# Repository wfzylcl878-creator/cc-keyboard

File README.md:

# CC-Keyboard — 6 键蓝牙小键盘

方向键 + 回车 + ESC 的紧凑蓝牙小键盘。布局（两行 + 右侧竖跨 2u 回车）：

```
┌───┐      ┌───┐
│ESC│  ↑   │ ↵ │
└───┘      │   │
┌───┬───┬───┐   │
│ ← │ ↓ │ → │   │
└───┴───┴───┤   │
            └───┘
┌───────────┴────────────────────┐
│ 电池   [SuperMini 横放 USB←]  开关 │  ← 底部凸出区
└────────────────────────────────┘
```

主控 SuperMini nRF52840（排针插接可拆卸，躺平在底部凸出区、USB 朝左），ZMK 固件，热插拔轴座。

## 目录结构

```
cc-keyboard/
├── ergogen/config.yaml      # PCB 生成配置（改布局/接线就改它）
├── output/                  # 生成产物（可随时重新生成）
│   ├── pcbs/main.kicad_pcb  #   PCB（嘉立创打样直接上传）
│   ├── outlines/plate.dxf   #   定位板（1.5mm 激光切割/CNC）
│   ├── outlines/plate.svg   #   定位板 SVG（切片软件 3D 打印用，导入后厚度设 1.5mm）
│   └── outlines/board.dxf   #   外壳参考轮廓
├── zmk-config/              # ZMK 固件配置（push 到 GitHub 自动编译）
│   ├── build.yaml           #   编译矩阵（板卡 + shield）
│   ├── west.yml             #   west manifest（CI 用，须在此层级）
│   ├── cc_keyboard.keymap   #   键位（可加层）
│   └── boards/shields/cc_keyboard/   # shield（zephyr 标准目录）
│       ├── cc_keyboard.overlay       #   6 键直连扫描 + 引脚
│       └── cc_keyboard.conf
└── .github/workflows/build.yml  # 固件 CI（Actions 自动编译）
```

## 重新生成 PCB

```bash
cd cc-keyboard
npx ergogen ergogen/config.yaml -o output --svg
python3 tools/postprocess.py   # PCB 数字规整+排母孔转通孔、SVG 填充清理
```

## 制造 / BOM（约 ¥80）

| 部件 | 规格 | 数量 |
|---|---|---|
| PCB | `output/pcbs/main_clean.kicad_pcb` 导入嘉立创 EDA 布线后下单（见下） | 1 |
| 定位板 | `output/outlines/plate.dxf`，1.5mm | 1 |
| SuperMini nRF52840 | 带 UF2 bootloader | 1 |
| 排针/排母 | 2.54mm（SuperMini 焊排针，PCB 焊排母，8+1 孔） | 各 1 |
| MX 热插拔座 | 已在 PCB footprint 内 | 6（随 PCB） |
| 轴体 | 任意 MX | 6 |
| 键帽 | 1u×5 + 竖 2u 回车键帽 | 6 |
| 电池 | PH2.0 插头，401230 (150mAh) | 1 |
| 电源开关 | MSK-12C02 拨动（或不装、锡桥短接） | 1 |

## PCB 布线与下单

**Ergogen 只做布局、不布线**——`main.kicad_pcb` 里没有任何铜走线（EDA 里看到的连线全是飞线），直接打样回来不能工作。流程：

1. 嘉立创 EDA（pro.lceda.cn）→ 文件 → 导入 → KiCad PCB → 选 `output/pcbs/main_clean.kicad_pcb`（数字规整版，直传下单页可能解析失败）
2. 布线（全部才 13 个连接，一把过）：
   - 信号线宽 0.25mm，电源线（`BAT_*`）0.5mm
   - GND 用整板敷铜（放置 → 整块敷铜 → 网络 GND），省 6 条线
   - 懒人直接用 EDA 的自动布线，完成后肉眼检查
3. 设计规则检查（DRC）通过后一键下单

## 接线表（PCB 排母孔 → SuperMini）

排母双排（孔距 2.54mm、排距 15.24mm，SuperMini 每排 13 脚），SuperMini 横放 USB 朝左、元件面朝上插入：

| 孔 | 网络 | SuperMini 引脚（该排从 USB 端数第几脚） |
|---|---|---|
| 行A·1 | B- | B-（第 1 脚） |
| 行A·2 | ESC | P0.06（第 2 脚） |
| 行A·3 | ↑ | P0.08（第 3 脚） |
| 行A·4 | GND | GND（第 4 脚，第 5 脚是第二个 GND 不放孔） |
| 行A·6 | ← | P0.17（第 6 脚） |
| 行A·7 | ↓ | P0.20（第 7 脚） |
| 行A·8 | → | P0.22（第 8 脚） |
| 行A·9 | ⏎ | P0.24（第 9 脚） |
| 行B·1 | B+ | B+（第 1 脚，电池正经开关后接入） |

行B 只有一个孔——插反 180° 时对不上孔，天然防呆。SuperMini 上只需在对应 9 个脚焊排针，其余脚悬空。
电池接 PCB 凸出区左段的 JST PH 座（免焊）；BAT+ 串凸出区右段的电源开关后进 SuperMini。

## 固件（ZMK）

1. push 本仓库到 GitHub（`.github/workflows/build.yml` 已就位，push 即自动编译）
2. Actions 自动编译 → 构建产物页下载 `firmware.uf2`
3. SuperMini 双击 RST → 弹出 USB 磁盘 → 拖入 uf2 → 完成
4. 系统蓝牙配对 "CC-Keyboard" 即可使用

改键位：编辑 `zmk-config/cc_keyboard.keymap`（bindings 顺序对应排针 1-6），push 后重新下载 uf2。

## 焊接顺序

1. 热插拔轴座（贴片，先焊一个脚对位再焊其余）
2. 排母（8+1 孔）、JST 座、开关焊盘
3. SuperMini 焊 9 根排针（对应接线表的脚），插排母测试
4. 验证：插 USB → CHG 灯亮；按键在 ZMK 下生效（直接连手机蓝牙试）
4. 验证：插 USB → CHG 灯亮；按键在 ZMK 下生效（`zmk-kconfig test` 或直接连手机蓝牙试）

## 已知取舍

- 回车是**热插拔轴**竖跨 2u，键帽需 1×2 竖键帽；无卫星轴孔（2u 竖键无卫星轴可接受，边缘按压略晃，介意可后续 rev2 加 stab 孔）
- `where` 过滤器使用 `/regex/` 斜杠格式（Ergogen 的字符串 where 是全等匹配，不是正则）
- Ergogen 稀疏布局：列内 `rows` 不能删行，须对要删的键写 `skip: true`；且行按**声明顺序**自 y=0 向上堆叠，全局 `rows` 必须把 `bottom` 写在 `top` 前，否则行名与实际位置颠倒

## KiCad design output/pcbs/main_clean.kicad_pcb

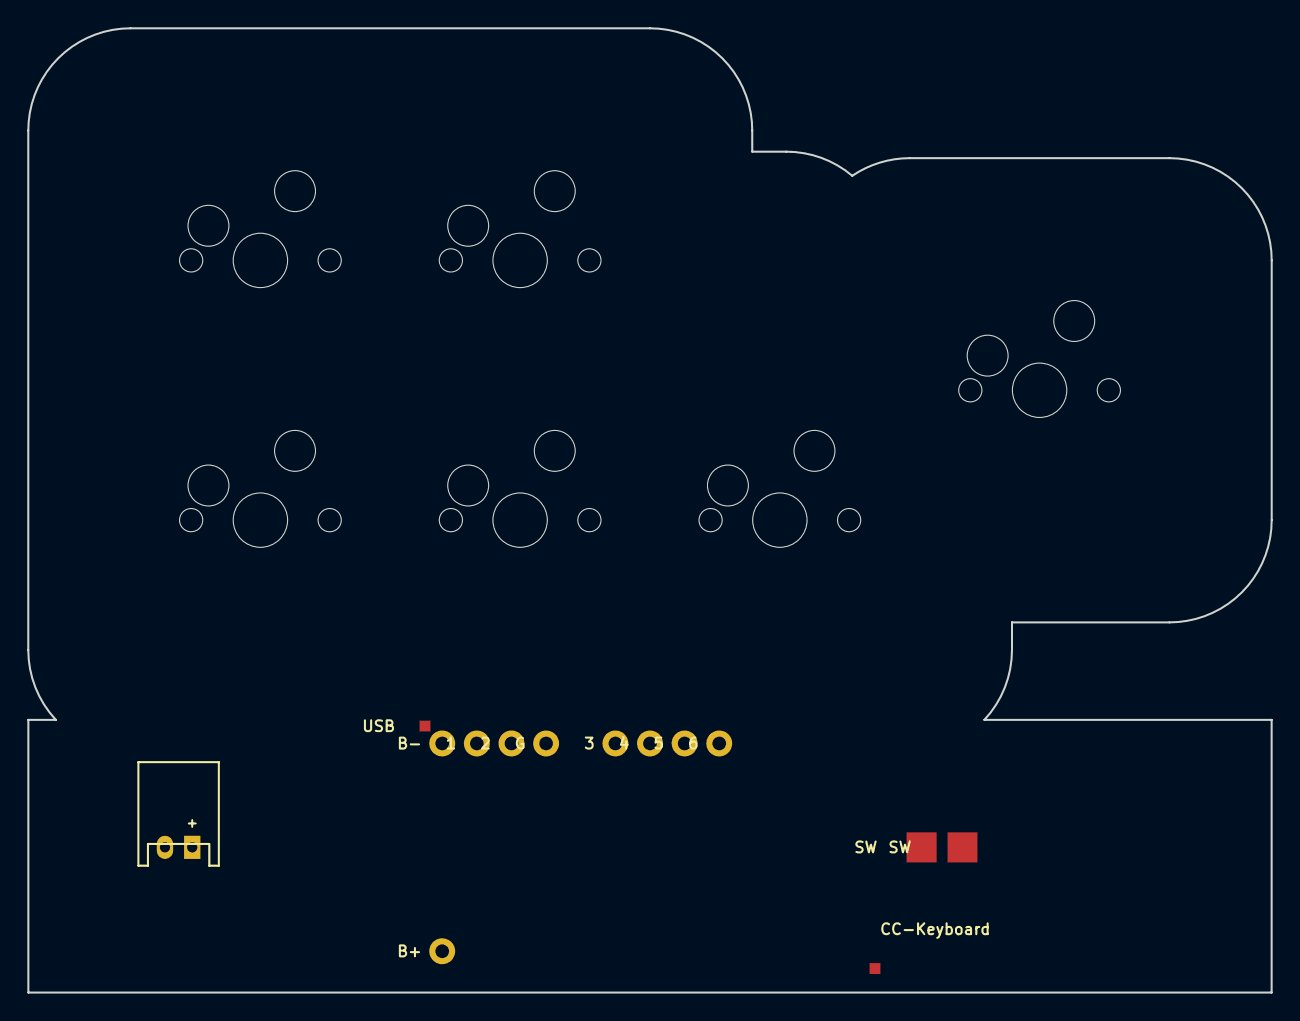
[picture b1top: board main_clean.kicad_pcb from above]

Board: 2 copper layers, 91.2 x 70.7 mm, 21 parts (0 on the bottom side), 10 nets, no tracks yet.

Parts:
JST1: JST_PH_S2B-PH-K_02x2.0mm_Angled
PAD1, PAD2, PAD3, PAD4, PAD5, PAD6, PAD7, PAD8, PAD9, PAD10, PAD11, PAD12, PAD13, PAD14: SMDPad
S1, S2, S3, S4, S5, S6: MX

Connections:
BAT_MINUS: JST1.2, PAD1.1
BAT_PLUS: JST1.1, PAD12.1
BAT_SWITCHED: PAD9.1, PAD13.1
GND: PAD4.1, S1.1, S2.1, S3.1, S4.1, S5.1, S6.1
KEY_DOWN: PAD6.1, S4.2
KEY_ENTER: PAD8.1, S6.2
KEY_ESC: PAD2.1, S1.2
KEY_LEFT: PAD5.1, S2.2
KEY_RIGHT: PAD7.1, S5.2
KEY_UP: PAD3.1, S3.2
